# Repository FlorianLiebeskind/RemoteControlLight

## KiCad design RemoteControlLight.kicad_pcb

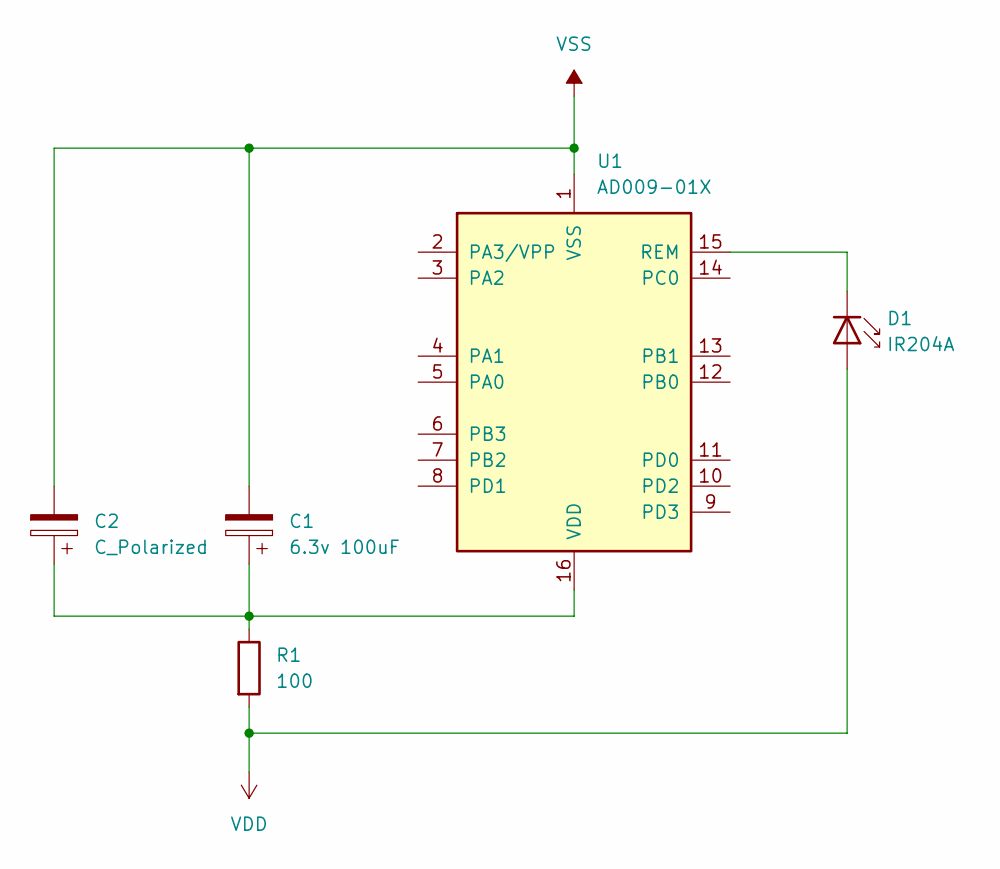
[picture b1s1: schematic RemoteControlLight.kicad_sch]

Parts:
C1: 6.3v 100uF; CP_Radial_D5.0mm_P2.00mm
C2: C_Polarized; C_0805_2012Metric
D1: IR204A; LED_D3.0mm_IRBlack
R1: 100; R_0805_2012Metric
U1: AD009-01X; SO-16_3.9x9.9mm_P1.27mm

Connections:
unnamed: D1.1 (K), U1.15 (REM)
unnamed: C1.1, C2.1, R1.1, U1.16 (VDD)
VDD: D1.2 (A), R1.2
VSS: C1.2, C2.2, U1.1 (VSS)

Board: 2 copper layers, 5 parts (0 on the bottom side), 4 nets, no tracks yet.

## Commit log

2025-03-24 no message
